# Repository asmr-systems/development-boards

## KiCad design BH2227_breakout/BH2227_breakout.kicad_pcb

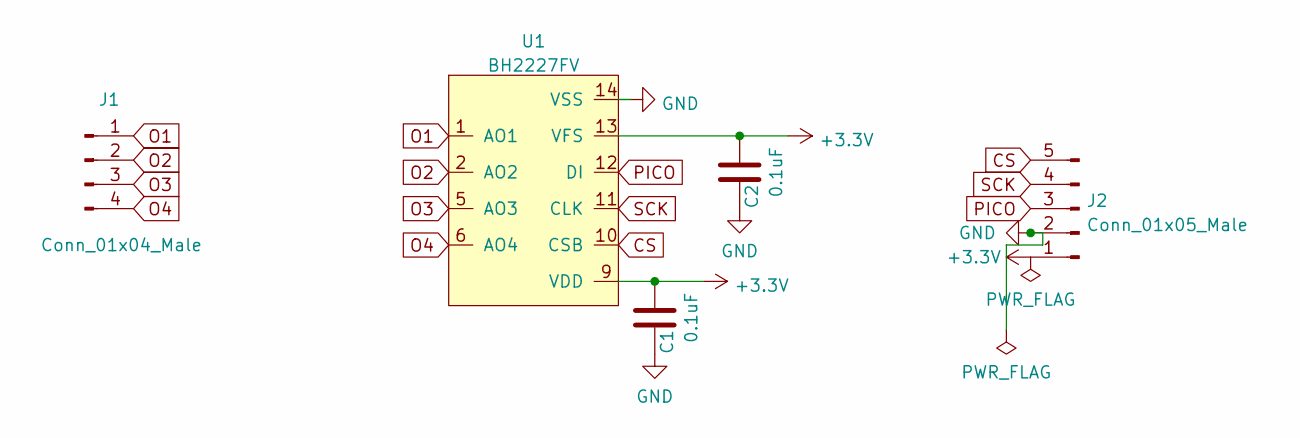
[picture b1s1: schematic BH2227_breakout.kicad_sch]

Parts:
C1, C2: 0.1uF; C_0402_1005Metric
J1: Conn_01x04_Male; PinHeader_1x04_P2.54mm_Vertical
J2: Conn_01x05_Male; PinHeader_1x05_P2.54mm_Vertical
U1: BH2227FV; SSOP-14_5.3x6.2mm_P0.65mm

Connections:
+3V3: C1.2, C2.2, J2.1, U1.9 (VDD), U1.13 (VFS)
CS: J2.5, U1.10 (CSB)
GND: C1.1, C2.1, J2.2, U1.14 (VSS)
O1: J1.1, U1.1 (AO1)
O2: J1.2, U1.2 (AO2)
O3: J1.3, U1.5 (AO3)
O4: J1.4, U1.6 (AO4)
PICO: J2.3, U1.12 (DI)
SCK: J2.4, U1.11 (CLK)

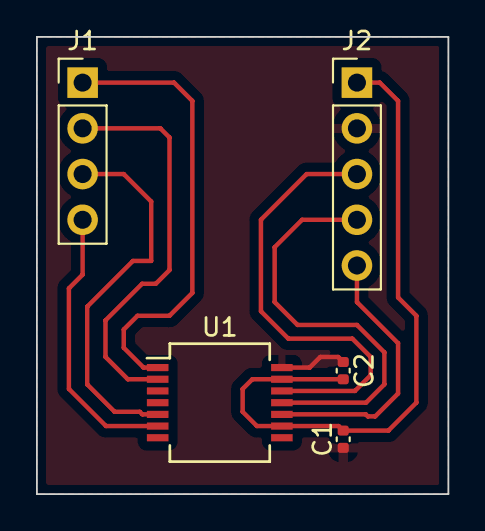
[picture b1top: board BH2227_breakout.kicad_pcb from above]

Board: 2 copper layers, 22.9 x 25.4 mm, 5 parts (0 on the bottom side), 9 nets.

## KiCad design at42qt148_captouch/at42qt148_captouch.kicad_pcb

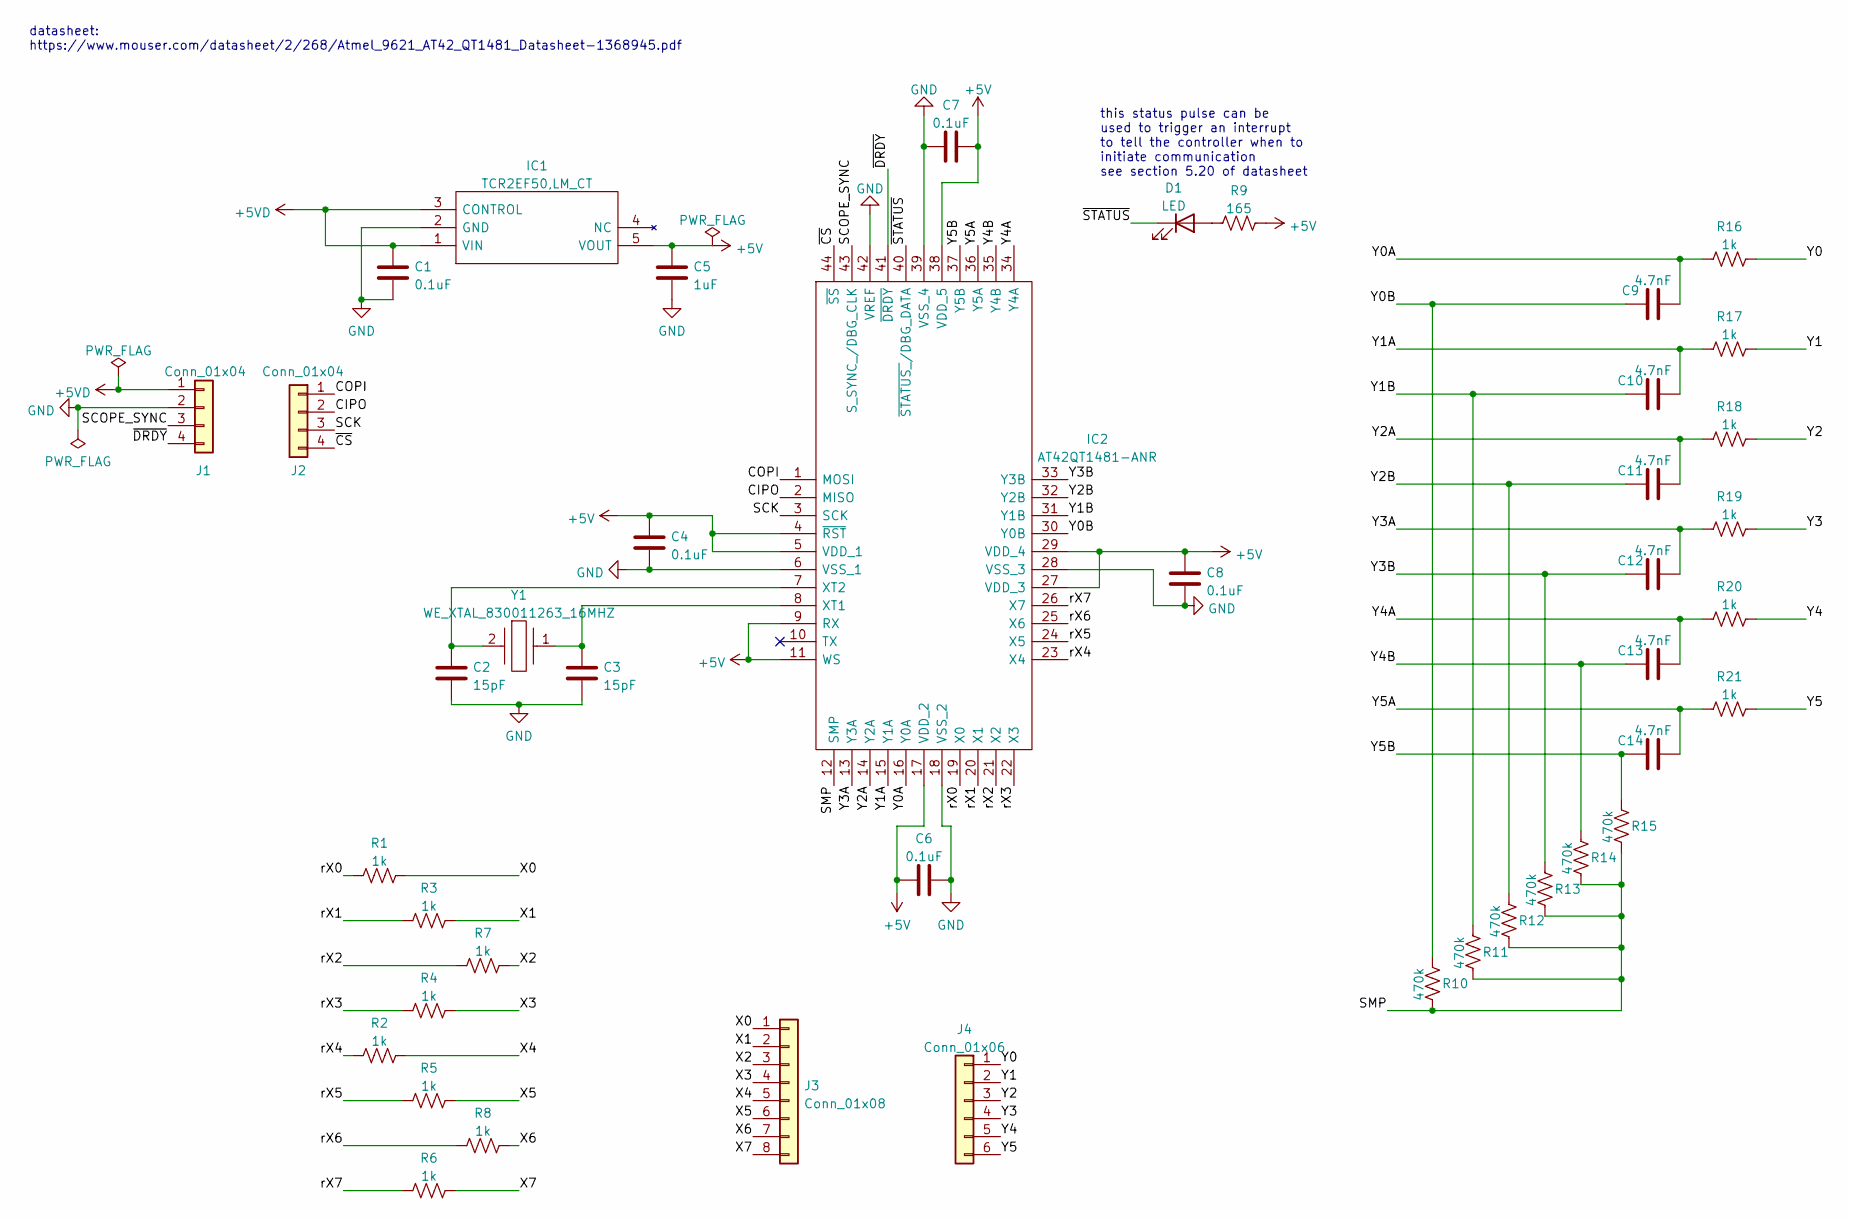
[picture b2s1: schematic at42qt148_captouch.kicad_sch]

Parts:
C1, C4, C6, C7, C8: 0.1uF; C_0603_1608Metric
C2, C3: 15pF; C_0603_1608Metric
C5: 1uF; C_0603_1608Metric
C9, C10, C11, C12, C13, C14: 4.7nF; C_0603_1608Metric
D1: LED; LED_0603_1608Metric
IC1: TCR2EF50,LM_CT; TCR2EF50LMCT; Mouser Part Number 757-TCR2EF50LMCT
IC2: AT42QT1481-ANR; QFP80P1200X1200X120-44N; Mouser Part Number 579-AT42QT1481-ANR
J1, J2: Conn_01x04; PinHeader_1x04_P2.54mm_Vertical
J3: Conn_01x08; PinSocket_1x08_P2.54mm_Vertical
J4: Conn_01x06; PinSocket_1x06_P2.54mm_Vertical
R1, R2, R3, R4, R5, R6, R7, R8, R16, R17, R18, R19, R20, R21: 1k; R_0603_1608Metric
R9: 165; R_0603_1608Metric
R10, R11, R12, R13, R14, R15: 470k; R_0603_1608Metric
Y1: WE_XTAL_830011263_16MHZ; Mouser Part Number 710-830011263

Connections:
+5V: C4.1, C5.1, C6.1, C7.2, C8.1, IC1.5 (VOUT), IC2.4 (~RST), IC2.5 (VDD_1), IC2.9 (RX), IC2.11 (WS), IC2.17 (VDD_2), IC2.27 (VDD_3), IC2.29 (VDD_4), IC2.38 (VDD_5), R9.2
+5VD: C1.1, IC1.1 (VIN), IC1.3 (CONTROL), J1.1
/CIPO: IC2.2 (MISO), J2.2
/COPI: IC2.1 (MOSI), J2.1
/SCK: IC2.3 (SCK), J2.3
/SCOPE_SYNC: IC2.43 (S_SYNC_/DBG_CLK), J1.3
/SMP: IC2.12 (SMP), R10.2, R11.2, R12.2, R13.2, R14.2, R15.2
/X0: J3.1, R1.2
/X1: J3.2, R3.2
/X2: J3.3, R7.2
/X3: J3.4, R4.2
/X4: J3.5, R2.2
/X5: J3.6, R5.2
/X6: J3.7, R8.2
/X7: J3.8, R6.2
/Y0: J4.1, R16.2
/Y0A: C9.2, IC2.16 (Y0A), R16.1
/Y0B: C9.1, IC2.30 (Y0B), R10.1
/Y1: J4.2, R17.2
/Y1A: C10.2, IC2.15 (Y1A), R17.1
/Y1B: C10.1, IC2.31 (Y1B), R11.1
/Y2: J4.3, R18.2
/Y2A: C11.2, IC2.14 (Y2A), R18.1
/Y2B: C11.1, IC2.32 (Y2B), R12.1
/Y3: J4.4, R19.2
/Y3A: C12.2, IC2.13 (Y3A), R19.1
/Y3B: C12.1, IC2.33 (Y3B), R13.1
/Y4: J4.5, R20.2
/Y4A: C13.2, IC2.34 (Y4A), R20.1
/Y4B: C13.1, IC2.35 (Y4B), R14.1
/Y5: J4.6, R21.2
/Y5A: C14.2, IC2.36 (Y5A), R21.1
/Y5B: C14.1, IC2.37 (Y5B), R15.1
/rX0: IC2.19 (X0), R1.1
/rX1: IC2.20 (X1), R3.1
/rX2: IC2.21 (X2), R7.1
/rX3: IC2.22 (X3), R4.1
/rX4: IC2.23 (X4), R2.1
/rX5: IC2.24 (X5), R5.1
/rX6: IC2.25 (X6), R8.1
/rX7: IC2.26 (X7), R6.1
/~CS: IC2.44 (~SS), J2.4
/~DRDY: IC2.41 (~DRDY), J1.4
/~STATUS: D1.1 (K), IC2.40 (~STATUS_/DBG_DATA)
GND: C1.2, C2.2, C3.2, C4.2, C5.2, C6.2, C7.1, C8.2, IC1.2 (GND), IC2.6 (VSS_1), IC2.18 (VSS_2), IC2.28 (VSS_3), IC2.39 (VSS_4), IC2.42 (VREF), J1.2
unnamed: C2.1, IC2.7 (XT2), Y1.2
unnamed: C3.1, IC2.8 (XT1), Y1.1
unnamed: D1.2 (A), R9.1

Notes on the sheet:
this status pulse can be used to trigger an interrupt to tell the controller when to initiate communication see section 5.20 of datasheet
datasheet: https://www.mouser.com/datasheet/2/268/Atmel_9621_AT42_QT1481_Datasheet-1368945.pdf

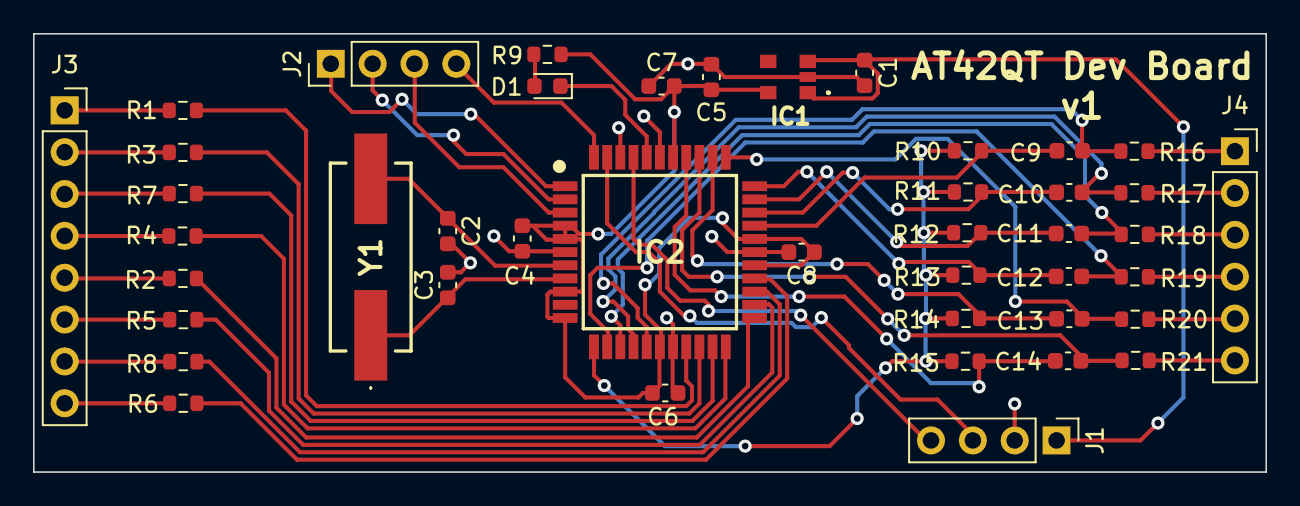
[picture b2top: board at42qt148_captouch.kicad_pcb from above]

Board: 2 copper layers, 74.8 x 26.6 mm, 43 parts (0 on the bottom side), 48 nets.

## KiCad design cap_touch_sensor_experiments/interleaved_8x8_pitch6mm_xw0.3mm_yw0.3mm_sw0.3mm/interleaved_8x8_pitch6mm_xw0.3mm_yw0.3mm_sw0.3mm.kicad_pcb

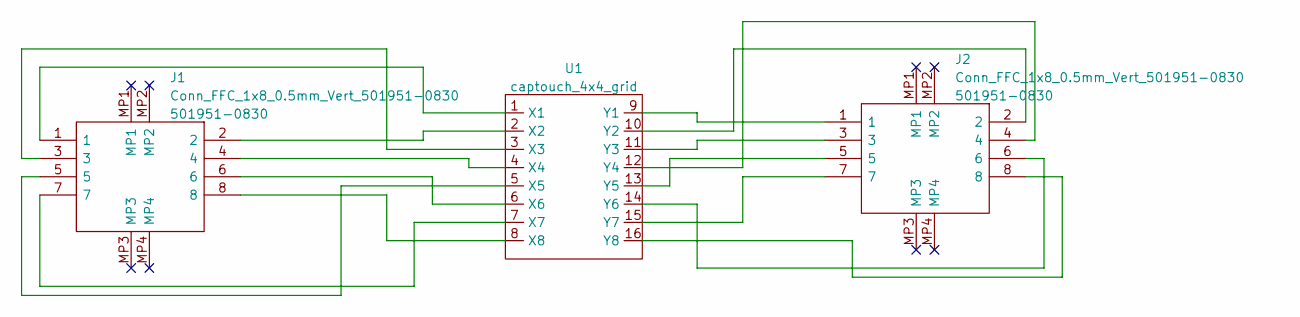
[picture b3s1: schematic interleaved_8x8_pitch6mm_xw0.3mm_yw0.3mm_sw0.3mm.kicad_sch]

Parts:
J1, J2: Conn_FFC_1x8_0.5mm_Vert_501951-0830; Conn_FFC_1x8_0.5mm_Molex_5019510830; Mouser Part Number 538-501951-0830
U1: captouch_4x4_grid; captouch_grid_4x4

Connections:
unnamed: J1.1, U1.1 (X1)
unnamed: J1.2, U1.2 (X2)
unnamed: J1.3, U1.3 (X3)
unnamed: J1.4, U1.4 (X4)
unnamed: J1.5, U1.5 (X5)
unnamed: J1.6, U1.6 (X6)
unnamed: J1.7, U1.7 (X7)
unnamed: J1.8, U1.8 (X8)
unnamed: J2.1, U1.9 (Y1)
unnamed: J2.2, U1.10 (Y2)
unnamed: J2.3, U1.11 (Y3)
unnamed: J2.4, U1.12 (Y4)
unnamed: J2.5, U1.13 (Y5)
unnamed: J2.6, U1.14 (Y6)
unnamed: J2.7, U1.15 (Y7)
unnamed: J2.8, U1.16 (Y8)

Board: 2 copper layers, 3 parts (0 on the bottom side), 16 nets, no tracks yet.

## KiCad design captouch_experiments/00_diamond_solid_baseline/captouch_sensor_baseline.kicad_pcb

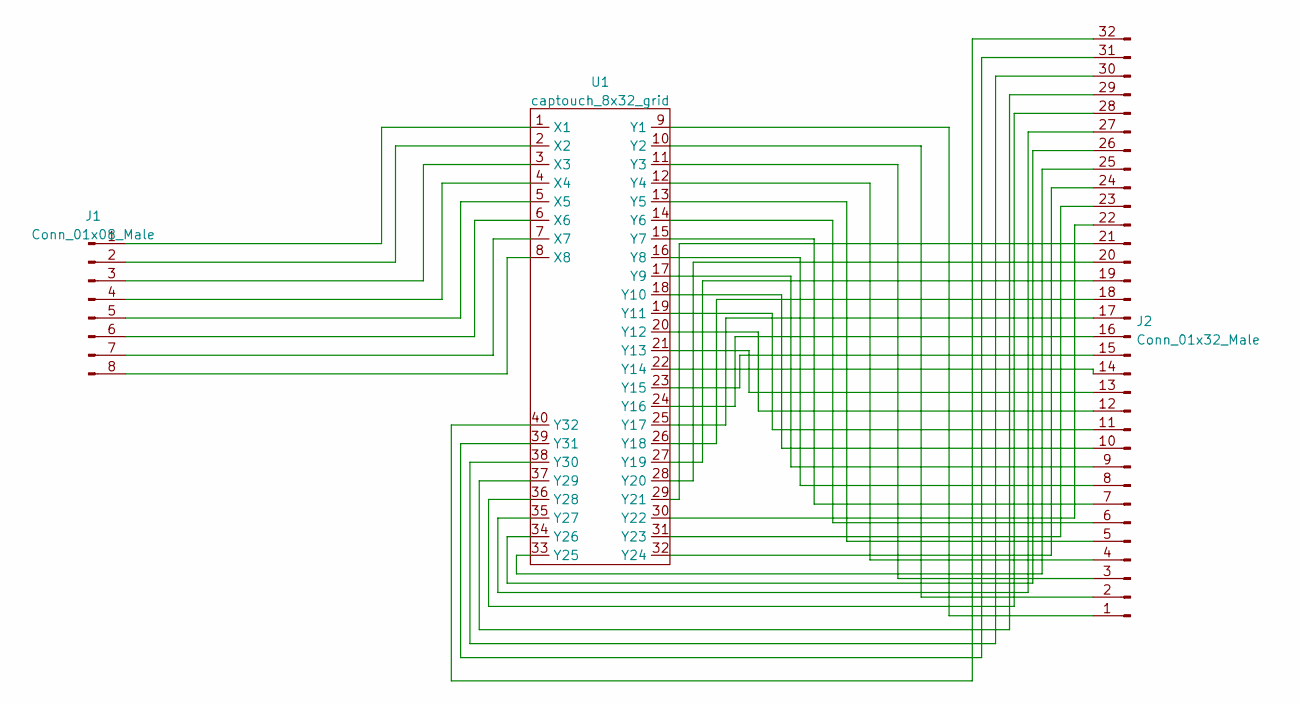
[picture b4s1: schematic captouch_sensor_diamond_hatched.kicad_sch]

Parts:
J1: Conn_01x08_Male; Conn_FFC_1x8_0.5mm_Molex_5019510830
J2: Conn_01x32_Male; Conn_FFC_1x32_0.5mm_Molex_5019513210
U1: captouch_8x32_grid; captouch_8x32_diamond_hatched

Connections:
unnamed: J1.1, U1.1 (X1)
unnamed: J1.2, U1.2 (X2)
unnamed: J1.3, U1.3 (X3)
unnamed: J1.4, U1.4 (X4)
unnamed: J1.5, U1.5 (X5)
unnamed: J1.6, U1.6 (X6)
unnamed: J1.7, U1.7 (X7)
unnamed: J1.8, U1.8 (X8)
unnamed: J2.1, U1.9 (Y1)
unnamed: J2.2, U1.10 (Y2)
unnamed: J2.3, U1.11 (Y3)
unnamed: J2.4, U1.12 (Y4)
unnamed: J2.5, U1.13 (Y5)
unnamed: J2.6, U1.14 (Y6)
unnamed: J2.7, U1.15 (Y7)
unnamed: J2.8, U1.16 (Y8)
unnamed: J2.9, U1.17 (Y9)
unnamed: J2.10, U1.18 (Y10)
unnamed: J2.11, U1.19 (Y11)
unnamed: J2.12, U1.20 (Y12)
unnamed: J2.13, U1.21 (Y13)
unnamed: J2.14, U1.22 (Y14)
unnamed: J2.15, U1.23 (Y15)
unnamed: J2.16, U1.24 (Y16)
unnamed: J2.17, U1.25 (Y17)
unnamed: J2.18, U1.26 (Y18)
unnamed: J2.19, U1.27 (Y19)
unnamed: J2.20, U1.28 (Y20)
unnamed: J2.21, U1.29 (Y21)
unnamed: J2.22, U1.30 (Y22)
unnamed: J2.23, U1.31 (Y23)
unnamed: J2.24, U1.32 (Y24)
unnamed: J2.25, U1.33 (Y25)
unnamed: J2.26, U1.34 (Y26)
unnamed: J2.27, U1.35 (Y27)
unnamed: J2.28, U1.36 (Y28)
unnamed: J2.29, U1.37 (Y29)
unnamed: J2.30, U1.38 (Y30)
unnamed: J2.31, U1.39 (Y31)
unnamed: J2.32, U1.40 (Y32)

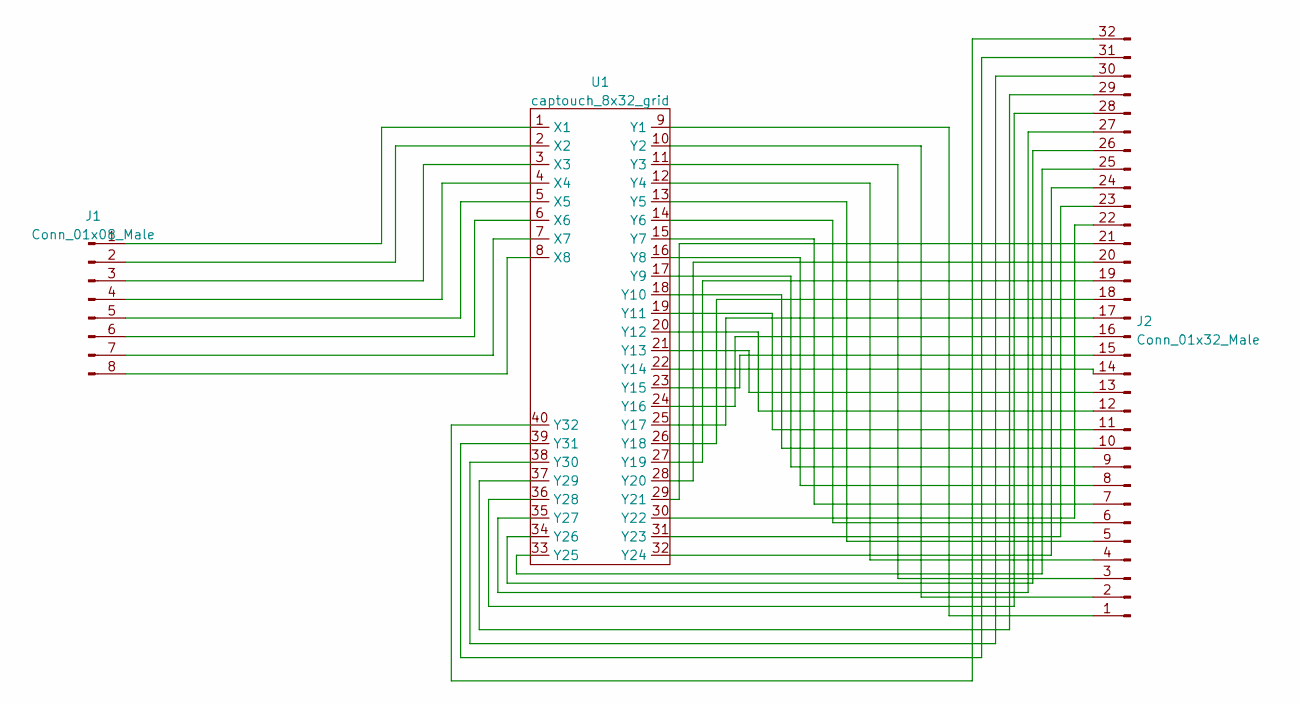
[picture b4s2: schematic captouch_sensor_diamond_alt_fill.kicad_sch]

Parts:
J1: Conn_01x08_Male; Conn_FFC_1x8_0.5mm_Molex_5019510830
J2: Conn_01x32_Male; Conn_FFC_1x32_0.5mm_Molex_5019513210
U1: captouch_8x32_grid; captouch_8x32_diamond_alt_fill

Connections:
unnamed: J1.1, U1.1 (X1)
unnamed: J1.2, U1.2 (X2)
unnamed: J1.3, U1.3 (X3)
unnamed: J1.4, U1.4 (X4)
unnamed: J1.5, U1.5 (X5)
unnamed: J1.6, U1.6 (X6)
unnamed: J1.7, U1.7 (X7)
unnamed: J1.8, U1.8 (X8)
unnamed: J2.1, U1.9 (Y1)
unnamed: J2.2, U1.10 (Y2)
unnamed: J2.3, U1.11 (Y3)
unnamed: J2.4, U1.12 (Y4)
unnamed: J2.5, U1.13 (Y5)
unnamed: J2.6, U1.14 (Y6)
unnamed: J2.7, U1.15 (Y7)
unnamed: J2.8, U1.16 (Y8)
unnamed: J2.9, U1.17 (Y9)
unnamed: J2.10, U1.18 (Y10)
unnamed: J2.11, U1.19 (Y11)
unnamed: J2.12, U1.20 (Y12)
unnamed: J2.13, U1.21 (Y13)
unnamed: J2.14, U1.22 (Y14)
unnamed: J2.15, U1.23 (Y15)
unnamed: J2.16, U1.24 (Y16)
unnamed: J2.17, U1.25 (Y17)
unnamed: J2.18, U1.26 (Y18)
unnamed: J2.19, U1.27 (Y19)
unnamed: J2.20, U1.28 (Y20)
unnamed: J2.21, U1.29 (Y21)
unnamed: J2.22, U1.30 (Y22)
unnamed: J2.23, U1.31 (Y23)
unnamed: J2.24, U1.32 (Y24)
unnamed: J2.25, U1.33 (Y25)
unnamed: J2.26, U1.34 (Y26)
unnamed: J2.27, U1.35 (Y27)
unnamed: J2.28, U1.36 (Y28)
unnamed: J2.29, U1.37 (Y29)
unnamed: J2.30, U1.38 (Y30)
unnamed: J2.31, U1.39 (Y31)
unnamed: J2.32, U1.40 (Y32)

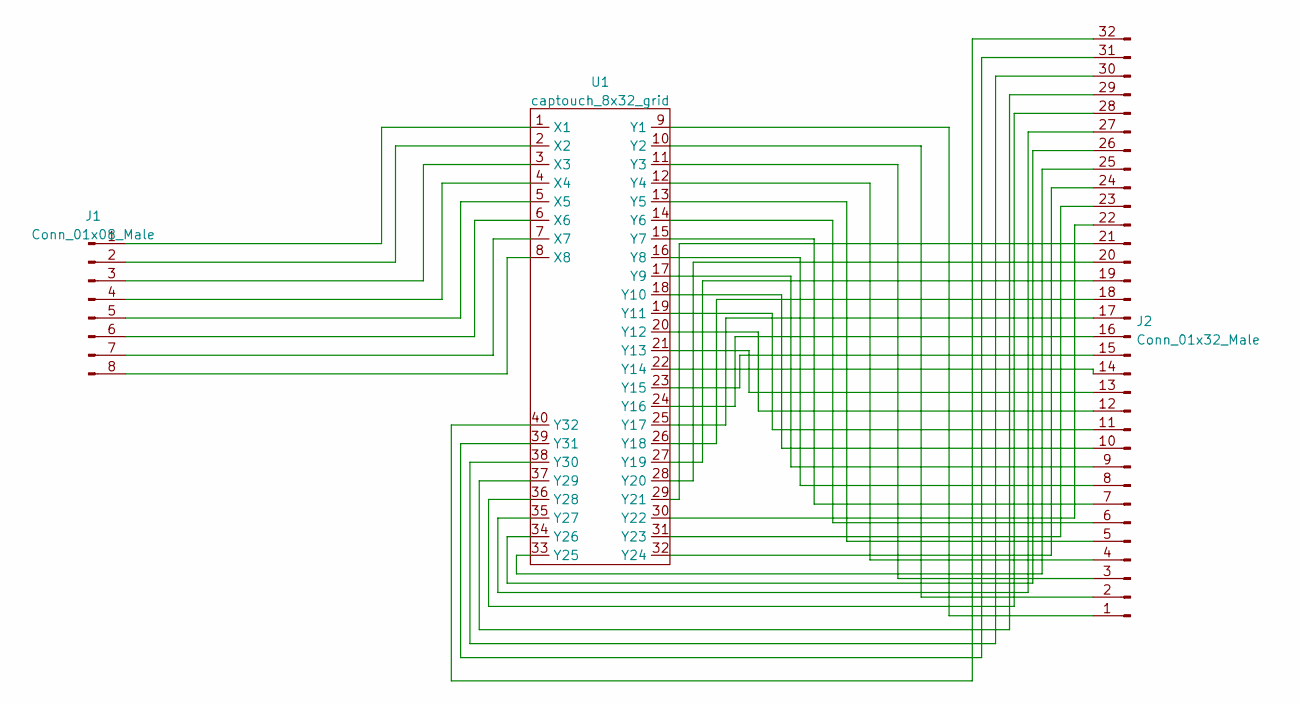
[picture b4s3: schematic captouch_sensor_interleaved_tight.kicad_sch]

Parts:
J1: Conn_01x08_Male; Conn_FFC_1x8_0.5mm_Molex_5019510830
J2: Conn_01x32_Male; Conn_FFC_1x32_0.5mm_Molex_5019513210
U1: captouch_8x32_grid; captouch_8x32_interleaved_tight

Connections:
unnamed: J1.1, U1.1 (X1)
unnamed: J1.2, U1.2 (X2)
unnamed: J1.3, U1.3 (X3)
unnamed: J1.4, U1.4 (X4)
unnamed: J1.5, U1.5 (X5)
unnamed: J1.6, U1.6 (X6)
unnamed: J1.7, U1.7 (X7)
unnamed: J1.8, U1.8 (X8)
unnamed: J2.1, U1.9 (Y1)
unnamed: J2.2, U1.10 (Y2)
unnamed: J2.3, U1.11 (Y3)
unnamed: J2.4, U1.12 (Y4)
unnamed: J2.5, U1.13 (Y5)
unnamed: J2.6, U1.14 (Y6)
unnamed: J2.7, U1.15 (Y7)
unnamed: J2.8, U1.16 (Y8)
unnamed: J2.9, U1.17 (Y9)
unnamed: J2.10, U1.18 (Y10)
unnamed: J2.11, U1.19 (Y11)
unnamed: J2.12, U1.20 (Y12)
unnamed: J2.13, U1.21 (Y13)
unnamed: J2.14, U1.22 (Y14)
unnamed: J2.15, U1.23 (Y15)
unnamed: J2.16, U1.24 (Y16)
unnamed: J2.17, U1.25 (Y17)
unnamed: J2.18, U1.26 (Y18)
unnamed: J2.19, U1.27 (Y19)
unnamed: J2.20, U1.28 (Y20)
unnamed: J2.21, U1.29 (Y21)
unnamed: J2.22, U1.30 (Y22)
unnamed: J2.23, U1.31 (Y23)
unnamed: J2.24, U1.32 (Y24)
unnamed: J2.25, U1.33 (Y25)
unnamed: J2.26, U1.34 (Y26)
unnamed: J2.27, U1.35 (Y27)
unnamed: J2.28, U1.36 (Y28)
unnamed: J2.29, U1.37 (Y29)
unnamed: J2.30, U1.38 (Y30)
unnamed: J2.31, U1.39 (Y31)
unnamed: J2.32, U1.40 (Y32)

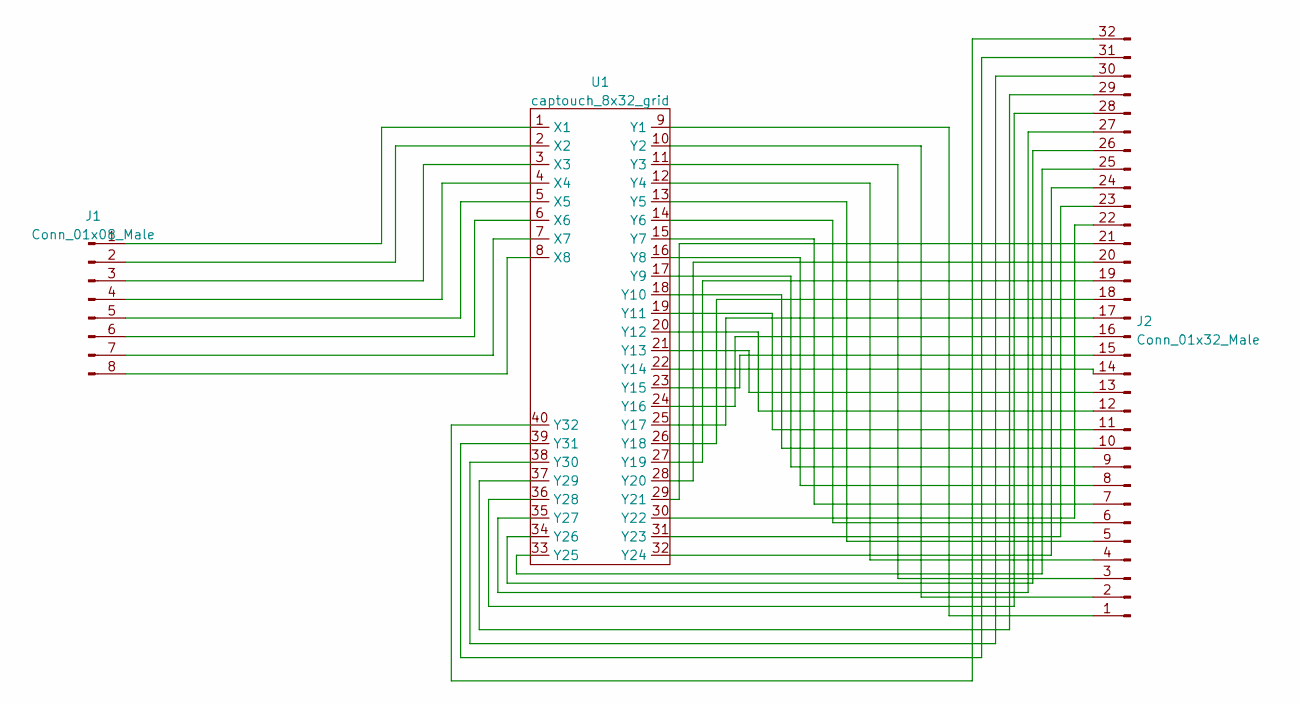
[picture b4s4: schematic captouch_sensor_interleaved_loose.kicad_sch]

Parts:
J1: Conn_01x08_Male; Conn_FFC_1x8_0.5mm_Molex_5019510830
J2: Conn_01x32_Male; Conn_FFC_1x32_0.5mm_Molex_5019513210
U1: captouch_8x32_grid; captouch_8x32_interleaved_loose

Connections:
unnamed: J1.1, U1.1 (X1)
unnamed: J1.2, U1.2 (X2)
unnamed: J1.3, U1.3 (X3)
unnamed: J1.4, U1.4 (X4)
unnamed: J1.5, U1.5 (X5)
unnamed: J1.6, U1.6 (X6)
unnamed: J1.7, U1.7 (X7)
unnamed: J1.8, U1.8 (X8)
unnamed: J2.1, U1.9 (Y1)
unnamed: J2.2, U1.10 (Y2)
unnamed: J2.3, U1.11 (Y3)
unnamed: J2.4, U1.12 (Y4)
unnamed: J2.5, U1.13 (Y5)
unnamed: J2.6, U1.14 (Y6)
unnamed: J2.7, U1.15 (Y7)
unnamed: J2.8, U1.16 (Y8)
unnamed: J2.9, U1.17 (Y9)
unnamed: J2.10, U1.18 (Y10)
unnamed: J2.11, U1.19 (Y11)
unnamed: J2.12, U1.20 (Y12)
unnamed: J2.13, U1.21 (Y13)
unnamed: J2.14, U1.22 (Y14)
unnamed: J2.15, U1.23 (Y15)
unnamed: J2.16, U1.24 (Y16)
unnamed: J2.17, U1.25 (Y17)
unnamed: J2.18, U1.26 (Y18)
unnamed: J2.19, U1.27 (Y19)
unnamed: J2.20, U1.28 (Y20)
unnamed: J2.21, U1.29 (Y21)
unnamed: J2.22, U1.30 (Y22)
unnamed: J2.23, U1.31 (Y23)
unnamed: J2.24, U1.32 (Y24)
unnamed: J2.25, U1.33 (Y25)
unnamed: J2.26, U1.34 (Y26)
unnamed: J2.27, U1.35 (Y27)
unnamed: J2.28, U1.36 (Y28)
unnamed: J2.29, U1.37 (Y29)
unnamed: J2.30, U1.38 (Y30)
unnamed: J2.31, U1.39 (Y31)
unnamed: J2.32, U1.40 (Y32)

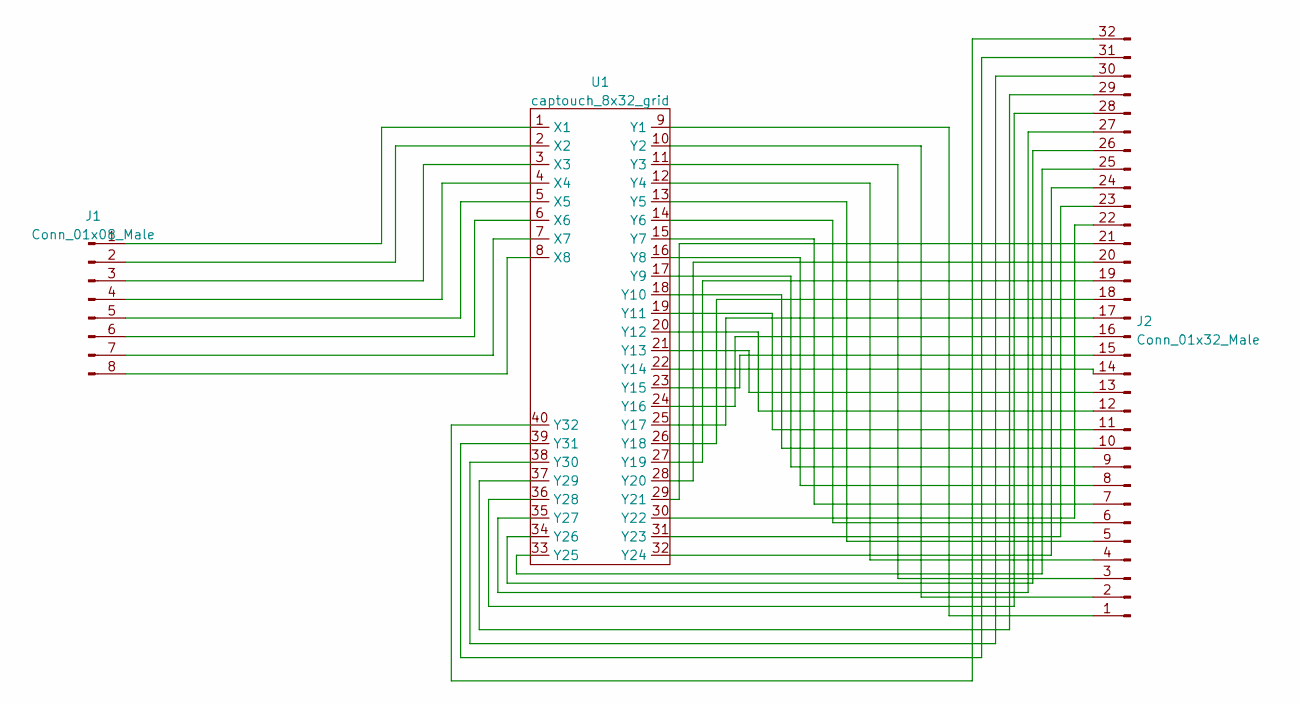
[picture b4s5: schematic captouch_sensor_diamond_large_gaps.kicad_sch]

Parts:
J1: Conn_01x08_Male; Conn_FFC_1x8_0.5mm_Molex_5019510830
J2: Conn_01x32_Male; Conn_FFC_1x32_0.5mm_Molex_5019513210
U1: captouch_8x32_grid; captouch_8x32_diamond_loose

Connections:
unnamed: J1.1, U1.1 (X1)
unnamed: J1.2, U1.2 (X2)
unnamed: J1.3, U1.3 (X3)
unnamed: J1.4, U1.4 (X4)
unnamed: J1.5, U1.5 (X5)
unnamed: J1.6, U1.6 (X6)
unnamed: J1.7, U1.7 (X7)
unnamed: J1.8, U1.8 (X8)
unnamed: J2.1, U1.9 (Y1)
unnamed: J2.2, U1.10 (Y2)
unnamed: J2.3, U1.11 (Y3)
unnamed: J2.4, U1.12 (Y4)
unnamed: J2.5, U1.13 (Y5)
unnamed: J2.6, U1.14 (Y6)
unnamed: J2.7, U1.15 (Y7)
unnamed: J2.8, U1.16 (Y8)
unnamed: J2.9, U1.17 (Y9)
unnamed: J2.10, U1.18 (Y10)
unnamed: J2.11, U1.19 (Y11)
unnamed: J2.12, U1.20 (Y12)
unnamed: J2.13, U1.21 (Y13)
unnamed: J2.14, U1.22 (Y14)
unnamed: J2.15, U1.23 (Y15)
unnamed: J2.16, U1.24 (Y16)
unnamed: J2.17, U1.25 (Y17)
unnamed: J2.18, U1.26 (Y18)
unnamed: J2.19, U1.27 (Y19)
unnamed: J2.20, U1.28 (Y20)
unnamed: J2.21, U1.29 (Y21)
unnamed: J2.22, U1.30 (Y22)
unnamed: J2.23, U1.31 (Y23)
unnamed: J2.24, U1.32 (Y24)
unnamed: J2.25, U1.33 (Y25)
unnamed: J2.26, U1.34 (Y26)
unnamed: J2.27, U1.35 (Y27)
unnamed: J2.28, U1.36 (Y28)
unnamed: J2.29, U1.37 (Y29)
unnamed: J2.30, U1.38 (Y30)
unnamed: J2.31, U1.39 (Y31)
unnamed: J2.32, U1.40 (Y32)

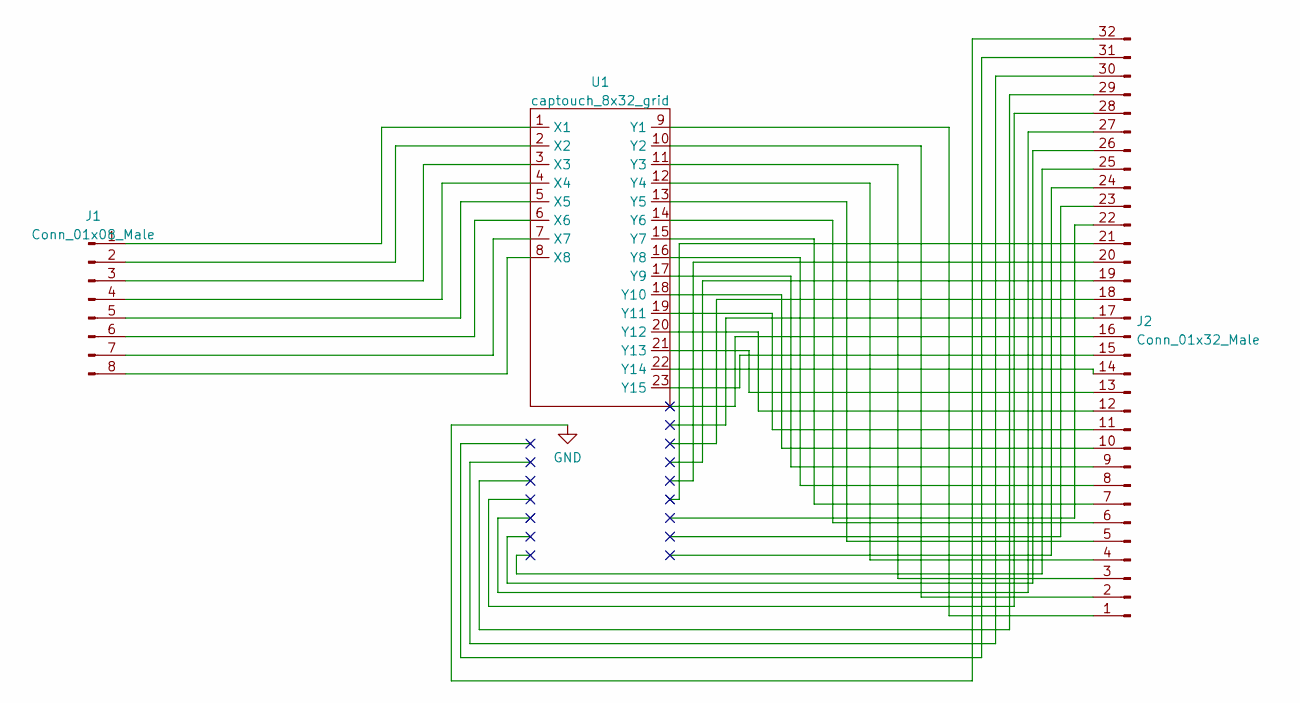
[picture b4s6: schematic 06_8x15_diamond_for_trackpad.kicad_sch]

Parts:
J1: Conn_01x08_Male; Conn_FFC_1x8_0.5mm_Molex_5019510830
J2: Conn_01x32_Male; Conn_FFC_1x32_0.5mm_Molex_5019513210
U1: captouch_8x32_grid; captouch_8x15_diamond_hatched_doubled

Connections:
unnamed: J1.1, U1.1 (X1)
unnamed: J1.2, U1.2 (X2)
unnamed: J1.3, U1.3 (X3)
unnamed: J1.4, U1.4 (X4)
unnamed: J1.5, U1.5 (X5)
unnamed: J1.6, U1.6 (X6)
unnamed: J1.7, U1.7 (X7)
unnamed: J1.8, U1.8 (X8)
unnamed: J2.1, U1.9 (Y1)
unnamed: J2.2, U1.10 (Y2)
unnamed: J2.3, U1.11 (Y3)
unnamed: J2.4, U1.12 (Y4)
unnamed: J2.5, U1.13 (Y5)
unnamed: J2.6, U1.14 (Y6)
unnamed: J2.7, U1.15 (Y7)
unnamed: J2.8, U1.16 (Y8)
unnamed: J2.9, U1.17 (Y9)
unnamed: J2.10, U1.18 (Y10)
unnamed: J2.11, U1.19 (Y11)
unnamed: J2.12, U1.20 (Y12)
unnamed: J2.13, U1.21 (Y13)
unnamed: J2.14, U1.22 (Y14)
unnamed: J2.15, U1.23 (Y15)
unnamed 23: J2.16; also elsewhere on the board
unnamed 24: J2.17; also elsewhere on the board
unnamed 25: J2.18; also elsewhere on the board
unnamed 26: J2.19; also elsewhere on the board
unnamed 27: J2.20; also elsewhere on the board
unnamed 28: J2.21; also elsewhere on the board
unnamed 29: J2.22; also elsewhere on the board
unnamed 30: J2.23; also elsewhere on the board
unnamed 31: J2.24; also elsewhere on the board
unnamed 32: J2.25; also elsewhere on the board
unnamed 33: J2.26; also elsewhere on the board
unnamed 34: J2.27; also elsewhere on the board
unnamed 35: J2.28; also elsewhere on the board
unnamed 36: J2.29; also elsewhere on the board
unnamed 37: J2.30; also elsewhere on the board
unnamed 38: J2.31; also elsewhere on the board
unnamed 39: J2.32; also elsewhere on the board

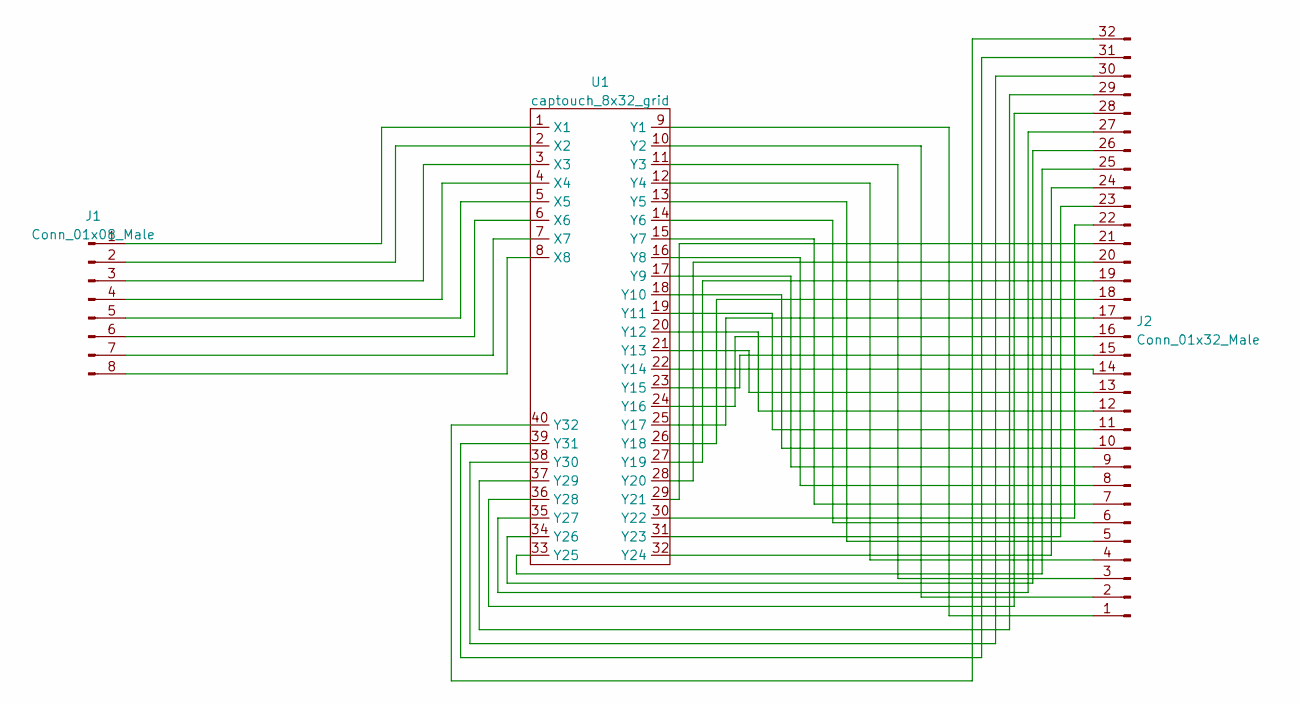
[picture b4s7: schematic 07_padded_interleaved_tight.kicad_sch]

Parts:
J1: Conn_01x08_Male; Conn_FFC_1x8_0.5mm_Molex_5019510830
J2: Conn_01x32_Male; Conn_FFC_1x32_0.5mm_Molex_5019513210
U1: captouch_8x32_grid; captouch_8x32_padded_interleaved

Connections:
unnamed: J1.1, U1.1 (X1)
unnamed: J1.2, U1.2 (X2)
unnamed: J1.3, U1.3 (X3)
unnamed: J1.4, U1.4 (X4)
unnamed: J1.5, U1.5 (X5)
unnamed: J1.6, U1.6 (X6)
unnamed: J1.7, U1.7 (X7)
unnamed: J1.8, U1.8 (X8)
unnamed: J2.1, U1.9 (Y1)
unnamed: J2.2, U1.10 (Y2)
unnamed: J2.3, U1.11 (Y3)
unnamed: J2.4, U1.12 (Y4)
unnamed: J2.5, U1.13 (Y5)
unnamed: J2.6, U1.14 (Y6)
unnamed: J2.7, U1.15 (Y7)
unnamed: J2.8, U1.16 (Y8)
unnamed: J2.9, U1.17 (Y9)
unnamed: J2.10, U1.18 (Y10)
unnamed: J2.11, U1.19 (Y11)
unnamed: J2.12, U1.20 (Y12)
unnamed: J2.13, U1.21 (Y13)
unnamed: J2.14, U1.22 (Y14)
unnamed: J2.15, U1.23 (Y15)
unnamed: J2.16, U1.24 (Y16)
unnamed: J2.17, U1.25 (Y17)
unnamed: J2.18, U1.26 (Y18)
unnamed: J2.19, U1.27 (Y19)
unnamed: J2.20, U1.28 (Y20)
unnamed: J2.21, U1.29 (Y21)
unnamed: J2.22, U1.30 (Y22)
unnamed: J2.23, U1.31 (Y23)
unnamed: J2.24, U1.32 (Y24)
unnamed: J2.25, U1.33 (Y25)
unnamed: J2.26, U1.34 (Y26)
unnamed: J2.27, U1.35 (Y27)
unnamed: J2.28, U1.36 (Y28)
unnamed: J2.29, U1.37 (Y29)
unnamed: J2.30, U1.38 (Y30)
unnamed: J2.31, U1.39 (Y31)
unnamed: J2.32, U1.40 (Y32)

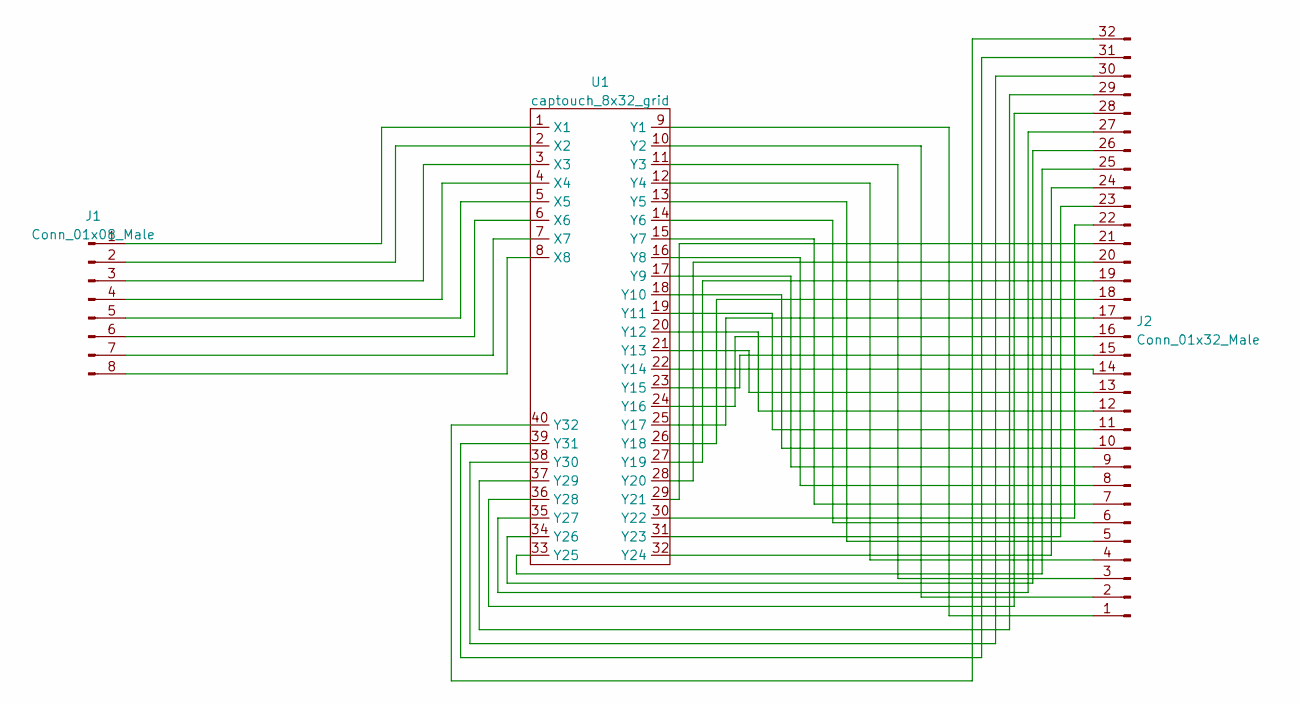
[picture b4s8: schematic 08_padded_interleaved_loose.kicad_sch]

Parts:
J1: Conn_01x08_Male; Conn_FFC_1x8_0.5mm_Molex_5019510830
J2: Conn_01x32_Male; Conn_FFC_1x32_0.5mm_Molex_5019513210
U1: captouch_8x32_grid; captouch_8x32_padded_interleaved_loose

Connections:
unnamed: J1.1, U1.1 (X1)
unnamed: J1.2, U1.2 (X2)
unnamed: J1.3, U1.3 (X3)
unnamed: J1.4, U1.4 (X4)
unnamed: J1.5, U1.5 (X5)
unnamed: J1.6, U1.6 (X6)
unnamed: J1.7, U1.7 (X7)
unnamed: J1.8, U1.8 (X8)
unnamed: J2.1, U1.9 (Y1)
unnamed: J2.2, U1.10 (Y2)
unnamed: J2.3, U1.11 (Y3)
unnamed: J2.4, U1.12 (Y4)
unnamed: J2.5, U1.13 (Y5)
unnamed: J2.6, U1.14 (Y6)
unnamed: J2.7, U1.15 (Y7)
unnamed: J2.8, U1.16 (Y8)
unnamed: J2.9, U1.17 (Y9)
unnamed: J2.10, U1.18 (Y10)
unnamed: J2.11, U1.19 (Y11)
unnamed: J2.12, U1.20 (Y12)
unnamed: J2.13, U1.21 (Y13)
unnamed: J2.14, U1.22 (Y14)
unnamed: J2.15, U1.23 (Y15)
unnamed: J2.16, U1.24 (Y16)
unnamed: J2.17, U1.25 (Y17)
unnamed: J2.18, U1.26 (Y18)
unnamed: J2.19, U1.27 (Y19)
unnamed: J2.20, U1.28 (Y20)
unnamed: J2.21, U1.29 (Y21)
unnamed: J2.22, U1.30 (Y22)
unnamed: J2.23, U1.31 (Y23)
unnamed: J2.24, U1.32 (Y24)
unnamed: J2.25, U1.33 (Y25)
unnamed: J2.26, U1.34 (Y26)
unnamed: J2.27, U1.35 (Y27)
unnamed: J2.28, U1.36 (Y28)
unnamed: J2.29, U1.37 (Y29)
unnamed: J2.30, U1.38 (Y30)
unnamed: J2.31, U1.39 (Y31)
unnamed: J2.32, U1.40 (Y32)

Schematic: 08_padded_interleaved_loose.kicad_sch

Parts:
J1: Conn_01x08_Male; Conn_FFC_1x8_0.5mm_Molex_5019510830
J2: Conn_01x32_Male; Conn_FFC_1x32_0.5mm_Molex_5019513210
U1: captouch_8x32_grid; captouch_8x32_padded_interleaved_loose_rx_masked

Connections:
unnamed: J1.1, U1.1 (X1)
unnamed: J1.2, U1.2 (X2)
unnamed: J1.3, U1.3 (X3)
unnamed: J1.4, U1.4 (X4)
unnamed: J1.5, U1.5 (X5)
unnamed: J1.6, U1.6 (X6)
unnamed: J1.7, U1.7 (X7)
unnamed: J1.8, U1.8 (X8)
unnamed: J2.1, U1.9 (Y1)
unnamed: J2.2, U1.10 (Y2)
unnamed: J2.3, U1.11 (Y3)
unnamed: J2.4, U1.12 (Y4)
unnamed: J2.5, U1.13 (Y5)
unnamed: J2.6, U1.14 (Y6)
unnamed: J2.7, U1.15 (Y7)
unnamed: J2.8, U1.16 (Y8)
unnamed: J2.9, U1.17 (Y9)
unnamed: J2.10, U1.18 (Y10)
unnamed: J2.11, U1.19 (Y11)
unnamed: J2.12, U1.20 (Y12)
unnamed: J2.13, U1.21 (Y13)
unnamed: J2.14, U1.22 (Y14)
unnamed: J2.15, U1.23 (Y15)
unnamed: J2.16, U1.24 (Y16)
unnamed: J2.17, U1.25 (Y17)
unnamed: J2.18, U1.26 (Y18)
unnamed: J2.19, U1.27 (Y19)
unnamed: J2.20, U1.28 (Y20)
unnamed: J2.21, U1.29 (Y21)
unnamed: J2.22, U1.30 (Y22)
unnamed: J2.23, U1.31 (Y23)
unnamed: J2.24, U1.32 (Y24)
unnamed: J2.25, U1.33 (Y25)
unnamed: J2.26, U1.34 (Y26)
unnamed: J2.27, U1.35 (Y27)
unnamed: J2.28, U1.36 (Y28)
unnamed: J2.29, U1.37 (Y29)
unnamed: J2.30, U1.38 (Y30)
unnamed: J2.31, U1.39 (Y31)
unnamed: J2.32, U1.40 (Y32)

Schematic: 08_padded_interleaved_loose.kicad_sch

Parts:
J1: Conn_01x08_Male; Conn_FFC_1x8_0.5mm_Molex_5019510830
J2: Conn_01x32_Male; Conn_FFC_1x32_0.5mm_Molex_5019513210
U1: captouch_8x32_grid; captouch_8x32_padded_interleaved_loose_all_masked

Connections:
unnamed: J1.1, U1.1 (X1)
unnamed: J1.2, U1.2 (X2)
unnamed: J1.3, U1.3 (X3)
unnamed: J1.4, U1.4 (X4)
unnamed: J1.5, U1.5 (X5)
unnamed: J1.6, U1.6 (X6)
unnamed: J1.7, U1.7 (X7)
unnamed: J1.8, U1.8 (X8)
unnamed: J2.1, U1.9 (Y1)
unnamed: J2.2, U1.10 (Y2)
unnamed: J2.3, U1.11 (Y3)
unnamed: J2.4, U1.12 (Y4)
unnamed: J2.5, U1.13 (Y5)
unnamed: J2.6, U1.14 (Y6)
unnamed: J2.7, U1.15 (Y7)
unnamed: J2.8, U1.16 (Y8)
unnamed: J2.9, U1.17 (Y9)
unnamed: J2.10, U1.18 (Y10)
unnamed: J2.11, U1.19 (Y11)
unnamed: J2.12, U1.20 (Y12)
unnamed: J2.13, U1.21 (Y13)
unnamed: J2.14, U1.22 (Y14)
unnamed: J2.15, U1.23 (Y15)
unnamed: J2.16, U1.24 (Y16)
unnamed: J2.17, U1.25 (Y17)
unnamed: J2.18, U1.26 (Y18)
unnamed: J2.19, U1.27 (Y19)
unnamed: J2.20, U1.28 (Y20)
unnamed: J2.21, U1.29 (Y21)
unnamed: J2.22, U1.30 (Y22)
unnamed: J2.23, U1.31 (Y23)
unnamed: J2.24, U1.32 (Y24)
unnamed: J2.25, U1.33 (Y25)
unnamed: J2.26, U1.34 (Y26)
unnamed: J2.27, U1.35 (Y27)
unnamed: J2.28, U1.36 (Y28)
unnamed: J2.29, U1.37 (Y29)
unnamed: J2.30, U1.38 (Y30)
unnamed: J2.31, U1.39 (Y31)
unnamed: J2.32, U1.40 (Y32)
